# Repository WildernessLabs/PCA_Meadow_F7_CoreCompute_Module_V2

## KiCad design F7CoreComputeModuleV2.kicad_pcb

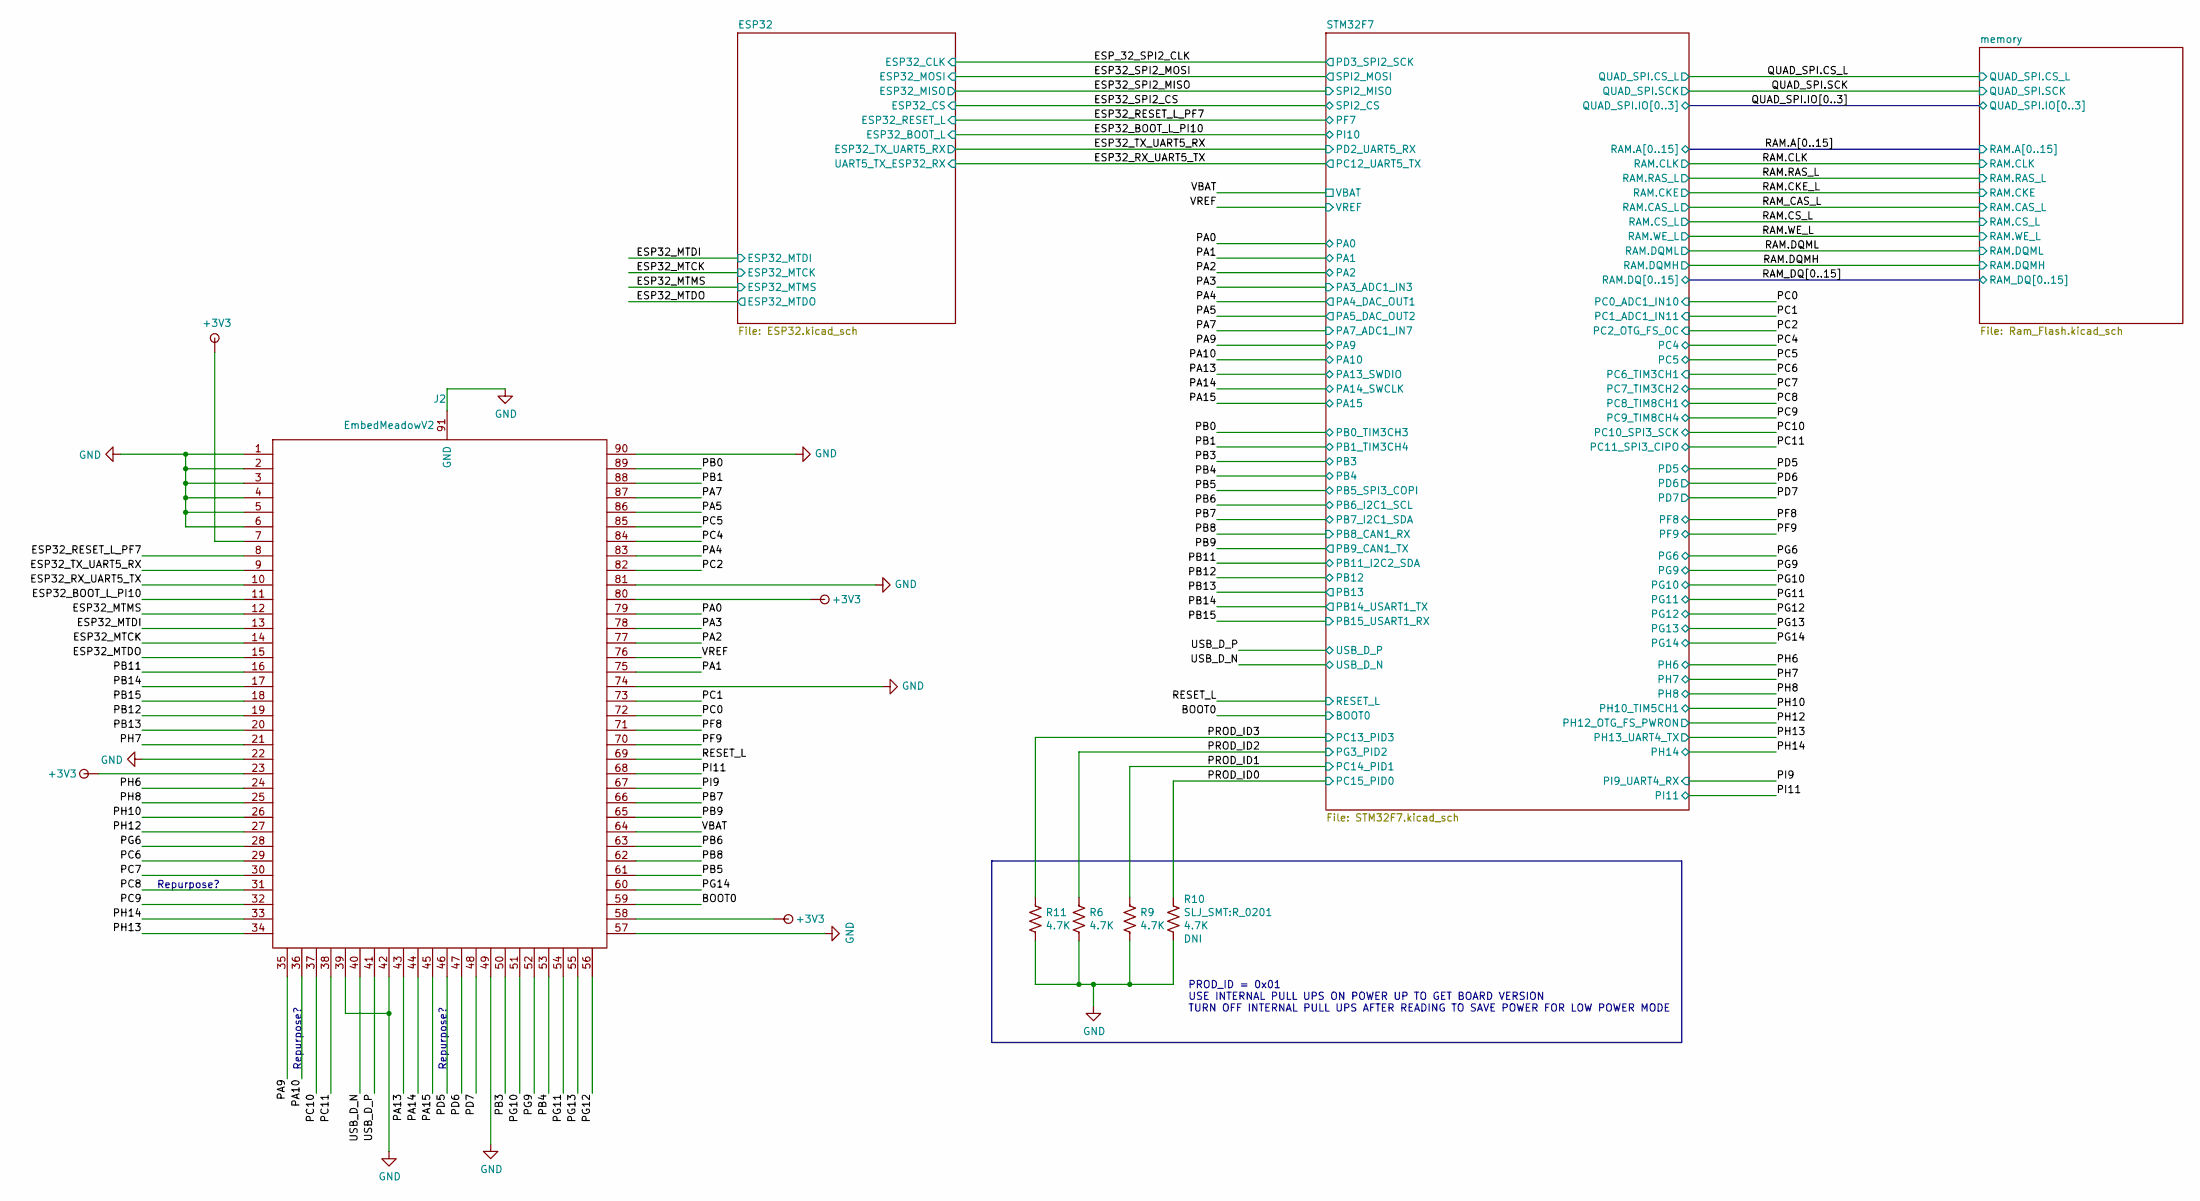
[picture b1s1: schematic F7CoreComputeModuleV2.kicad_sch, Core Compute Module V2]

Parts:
J2: EmbedMeadowV2; MeadowEmbededV2_OnModule
R6, R9, R10, R11: R_4K7_1%_0201; R_0201

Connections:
+3V3: J2.7, J2.23, J2.58, J2.80; also elsewhere on the board
/BOOT0: J2.59; also elsewhere on the board
/ESP32_BOOT_L_PI10: J2.11; also elsewhere on the board
/ESP32_MTCK: J2.14; also elsewhere on the board
/ESP32_MTDI: J2.13; also elsewhere on the board
/ESP32_MTDO: J2.15; also elsewhere on the board
/ESP32_MTMS: J2.12; also elsewhere on the board
/ESP32_RESET_L_PF7: J2.8; also elsewhere on the board
/ESP32_RX_UART5_TX: J2.10; also elsewhere on the board
/ESP32_TX_UART5_RX: J2.9; also elsewhere on the board
/PA0: J2.79; also elsewhere on the board
/PA1: J2.75; also elsewhere on the board
/PA2: J2.77; also elsewhere on the board
/PA3: J2.78; also elsewhere on the board
/PA4: J2.83; also elsewhere on the board
/PA5: J2.86; also elsewhere on the board
/PA7: J2.87; also elsewhere on the board
/PA9: J2.35; also elsewhere on the board
/PA10: J2.36; also elsewhere on the board
/PA13: J2.43; also elsewhere on the board
/PA14: J2.44; also elsewhere on the board
/PA15: J2.45; also elsewhere on the board
/PB0: J2.89; also elsewhere on the board
/PB1: J2.88; also elsewhere on the board
/PB3: J2.50; also elsewhere on the board
/PB4: J2.53; also elsewhere on the board
/PB5: J2.61; also elsewhere on the board
/PB6: J2.63; also elsewhere on the board
/PB7: J2.66; also elsewhere on the board
/PB8: J2.62; also elsewhere on the board
/PB9: J2.65; also elsewhere on the board
/PB11: J2.16; also elsewhere on the board
/PB12: J2.19; also elsewhere on the board
/PB13: J2.20; also elsewhere on the board
/PB14: J2.17; also elsewhere on the board
/PB15: J2.18; also elsewhere on the board
/PC0: J2.72; also elsewhere on the board
/PC1: J2.73; also elsewhere on the board
/PC2: J2.82; also elsewhere on the board
/PC4: J2.84; also elsewhere on the board
/PC5: J2.85; also elsewhere on the board
/PC6: J2.29; also elsewhere on the board
/PC7: J2.30; also elsewhere on the board
/PC8: J2.31; also elsewhere on the board
/PC9: J2.32; also elsewhere on the board
/PC10: J2.37; also elsewhere on the board
/PC11: J2.38; also elsewhere on the board
/PD5: J2.46; also elsewhere on the board
/PD6: J2.47; also elsewhere on the board
/PD7: J2.48; also elsewhere on the board
/PF8: J2.71; also elsewhere on the board
/PF9: J2.70; also elsewhere on the board
/PG6: J2.28; also elsewhere on the board
/PG9: J2.52; also elsewhere on the board
/PG10: J2.51; also elsewhere on the board
/PG11: J2.54; also elsewhere on the board
/PG12: J2.56; also elsewhere on the board
/PG13: J2.55; also elsewhere on the board
/PG14: J2.60; also elsewhere on the board
/PH6: J2.24; also elsewhere on the board
/PH7: J2.21; also elsewhere on the board
/PH8: J2.25; also elsewhere on the board
/PH10: J2.26; also elsewhere on the board
/PH12: J2.27; also elsewhere on the board
/PH13: J2.34; also elsewhere on the board
/PH14: J2.33; also elsewhere on the board
/PI9: J2.67; also elsewhere on the board
/PI11: J2.68; also elsewhere on the board
/PROD_ID0: R10.1; also elsewhere on the board
/PROD_ID1: R9.1; also elsewhere on the board
/PROD_ID2: R6.1; also elsewhere on the board
/PROD_ID3: R11.1; also elsewhere on the board
/RESET_L: J2.69; also elsewhere on the board
/USB_D_N: J2.40; also elsewhere on the board
/USB_D_P: J2.41; also elsewhere on the board
/VBAT: J2.64; also elsewhere on the board
/VREF: J2.76; also elsewhere on the board
GND: J2.1, J2.2, J2.3, J2.4, J2.5, J2.6, J2.22, J2.39, J2.42, J2.49, J2.57, J2.74, J2.81, J2.90, J2.91 (GND), R6.2, R9.2, R10.2, R11.2; also elsewhere on the board

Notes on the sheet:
PROD_ID = 0x01 USE INTERNAL PULL UPS ON POWER UP TO GET BOARD VERSION TURN OFF INTERNAL PULL UPS AFTER READING TO SAVE POWER FOR LOW POWER MODE
Repurpose?

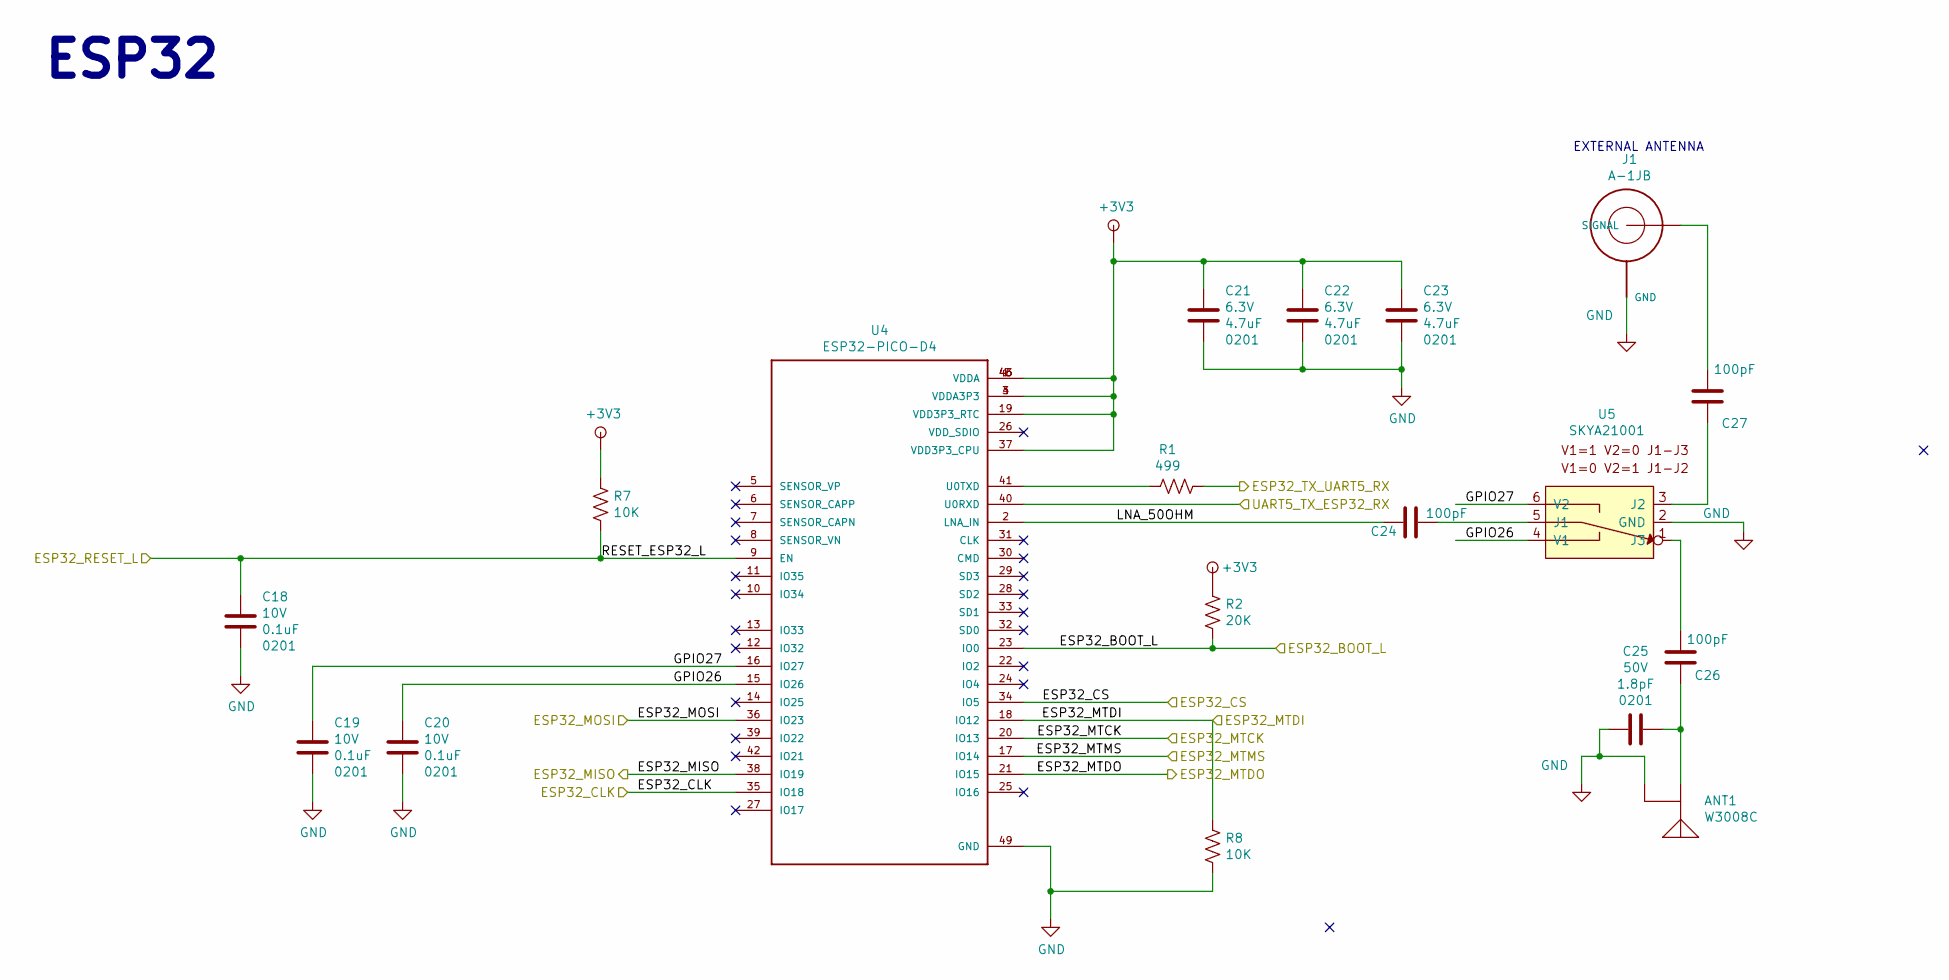
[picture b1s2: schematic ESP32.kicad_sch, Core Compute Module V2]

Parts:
ANT1: W3008C; ANTENNA_W3008C_B
C18, C19, C20: C_0201_0.1UF_10V_X5R; C_0201; Voltage 10V; Tolerance 10%
C21, C22, C23: C_0201_4.7UF_6.3V_X5R; C_0201; Voltage 6.3V; Tolerance 20%
C24, C26, C27: C_0201_100PF_50V_C0G; C_0201; Voltage 50V; Tolerance 5%
C25: C_0201_1.8pF_50V_C0G; C_0201; Voltage 50V; Tolerance 0.25pF
J1: A-1JB; AMPHENOL_A-1JB
R1: R_499_1%_0201; R_0201
R2: R_20K_1%_0201; R_0201
R7, R8: R_10K_1%_0201; R_0201
U4: ESP32-PICO-D4; PQFN50P700X700X104-49N
U5: SKYA21001; SOT-363_SC-70-6

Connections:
+3V3: C21.1, C22.1, C23.1, R2.1, R7.1, U4.1 (VDDA), U4.3 (VDDA3P3), U4.4 (VDDA3P3), U4.19 (VDD3P3_RTC), U4.37 (VDD3P3_CPU), U4.43 (VDDA), U4.46 (VDDA); also elsewhere on the board
/ESP32/GPIO26: C20.1, U4.15 (IO26), U5.4 (V1)
/ESP32/GPIO27: C19.1, U4.16 (IO27), U5.6 (V2)
/ESP32/LNA_50OHM: C24.2, U4.2 (LNA_IN)
/ESP32_BOOT_L_PI10: R2.2, U4.23 (IO0); also elsewhere on the board
/ESP32_MTCK: U4.20 (IO13); also elsewhere on the board
/ESP32_MTDI: R8.1, U4.18 (IO12); also elsewhere on the board
/ESP32_MTDO: U4.21 (IO15); also elsewhere on the board
/ESP32_MTMS: U4.17 (IO14); also elsewhere on the board
/ESP32_RESET_L_PF7: C18.1, R7.2, U4.9 (EN); also elsewhere on the board
/ESP32_RX_UART5_TX: U4.40 (U0RXD); also elsewhere on the board
/ESP32_SPI2_CS: U4.34 (IO5); also elsewhere on the board
/ESP32_SPI2_MISO: U4.38 (IO19); also elsewhere on the board
/ESP32_SPI2_MOSI: U4.36 (IO23); also elsewhere on the board
/ESP32_TX_UART5_RX: R1.1; also elsewhere on the board
/ESP_32_SPI2_CLK: U4.35 (IO18); also elsewhere on the board
GND: ANT1.G1 (GND), ANT1.G2 (GND), C18.2, C19.2, C20.2, C21.2, C22.2, C23.2, C25.2, J1.GND1 (GND), J1.GND2 (GND), J1.OPTIONAL_GND (GND), R8.2, U4.49 (GND), U5.2 (GND); also elsewhere on the board
unnamed: ANT1.FEED, C25.1, C26.1
unnamed: C24.1, U5.5 (J1)
unnamed: C26.2, U5.1 (J3)
unnamed: C27.1, U5.3 (J2)
unnamed: C27.2, J1.SIGNAL
unnamed: R1.2, U4.41 (U0TXD)

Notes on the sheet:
ESP32
EXTERNAL ANTENNA

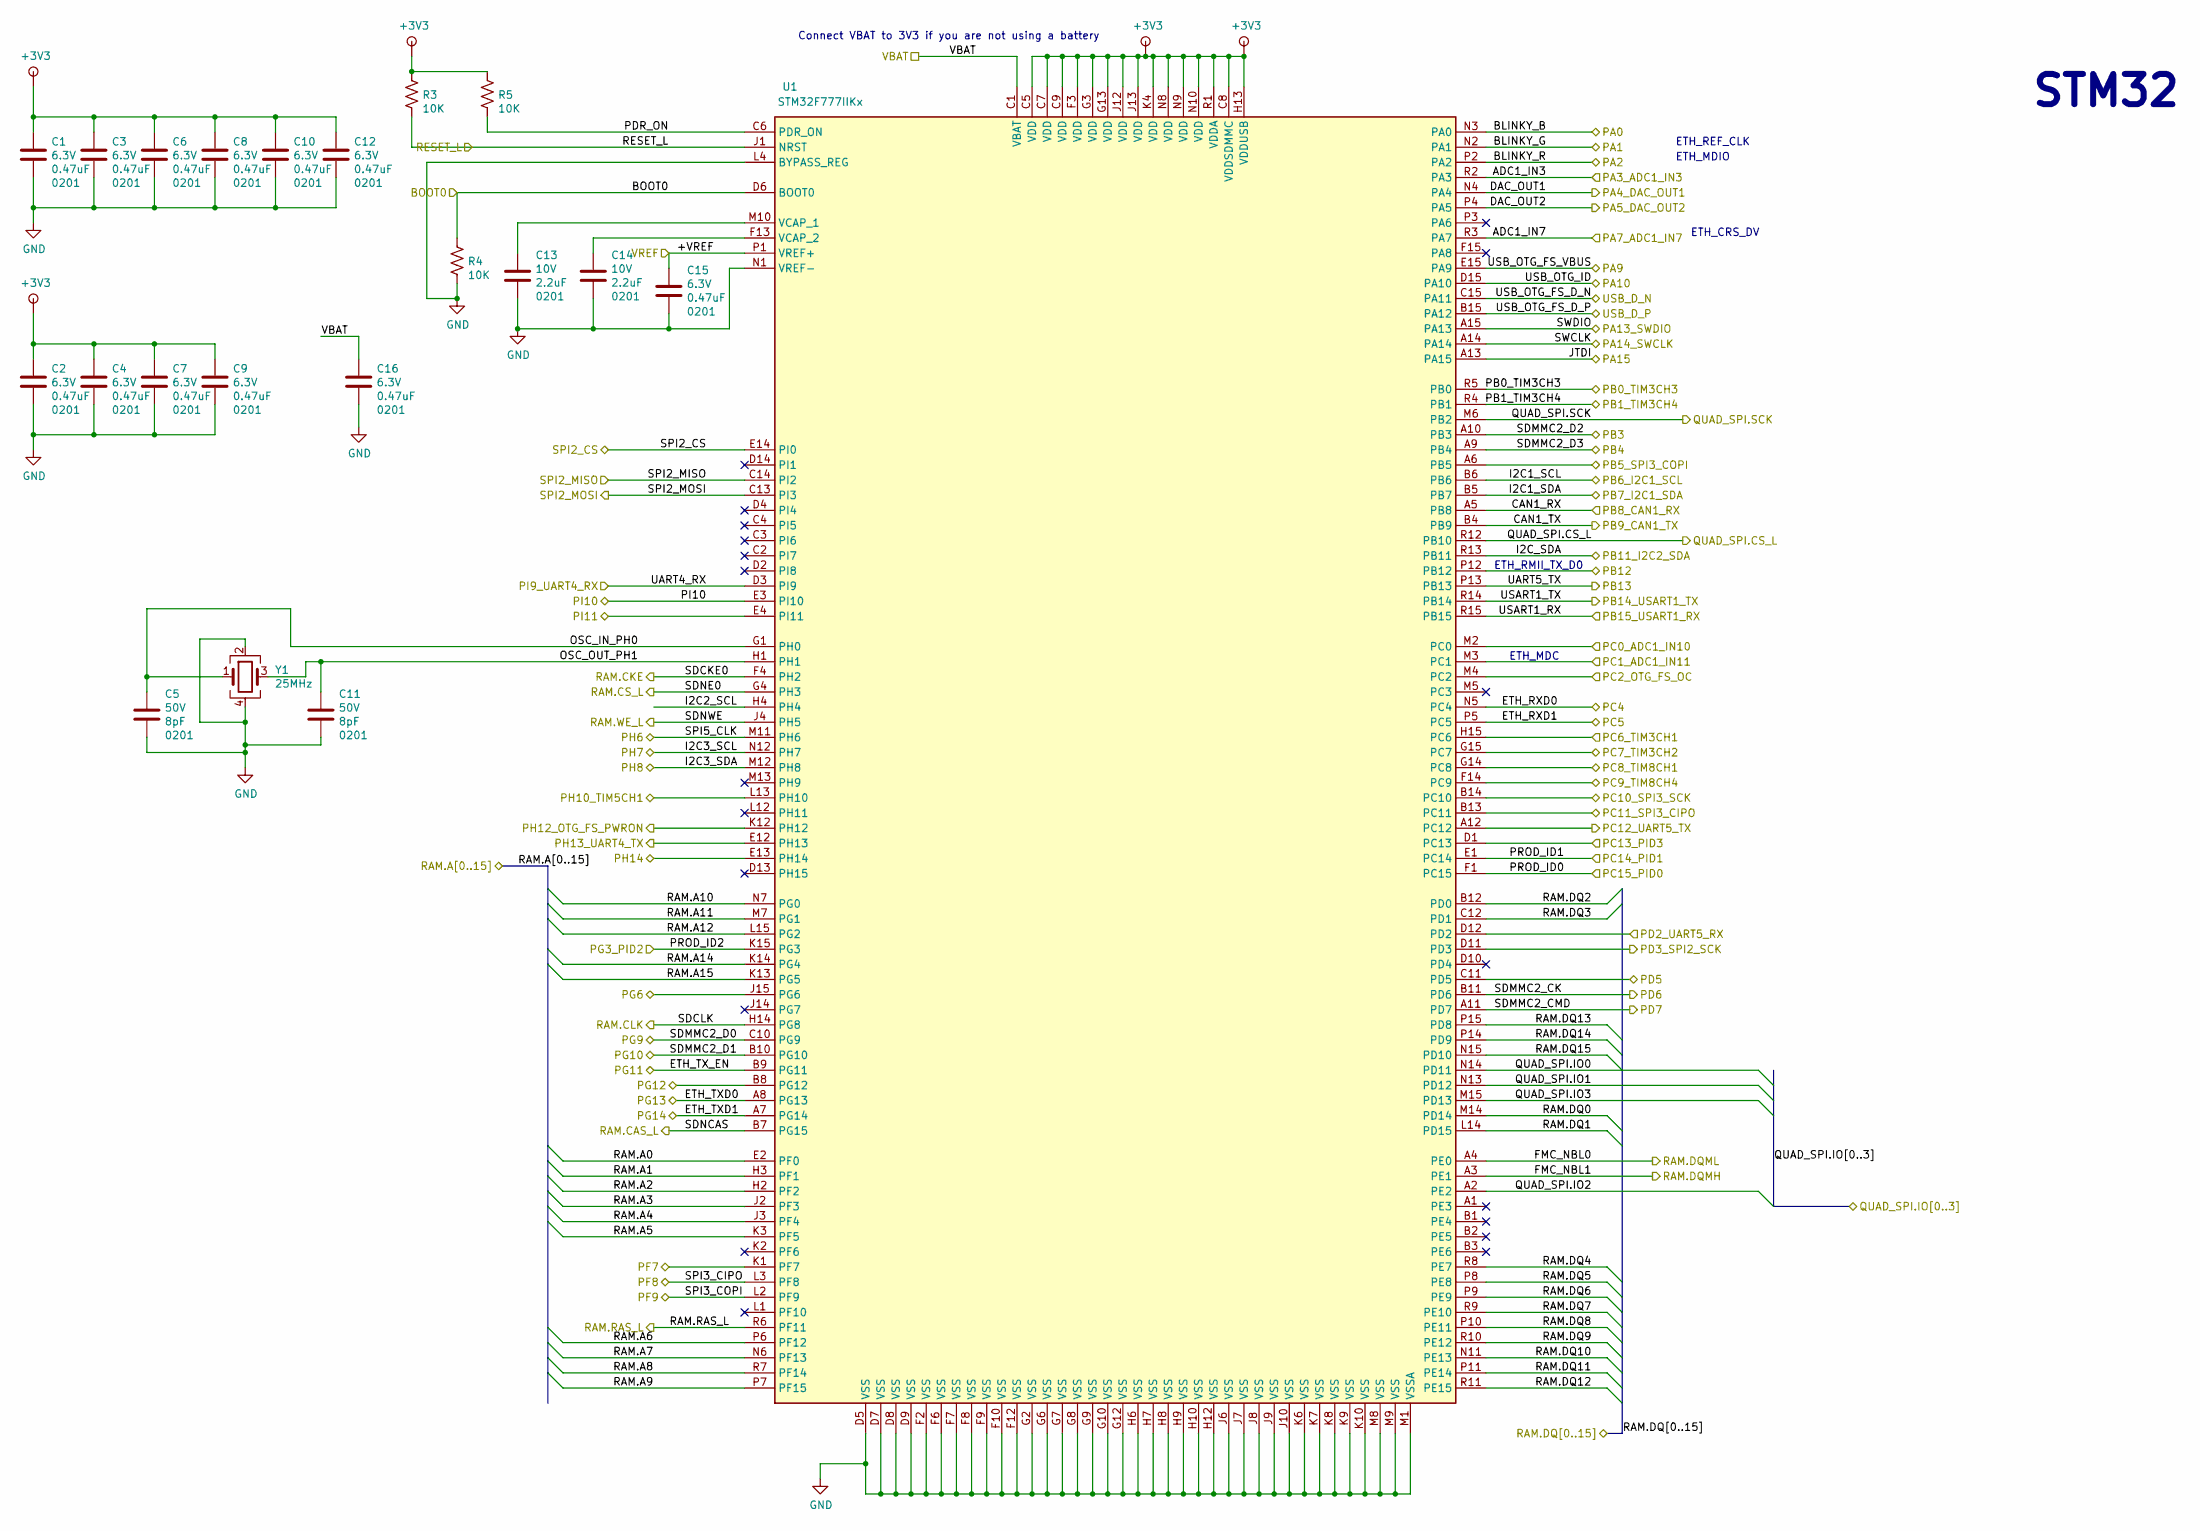
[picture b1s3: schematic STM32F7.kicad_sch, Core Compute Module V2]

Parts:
C1, C2, C3, C4, C6, C7, C8, C9, C10, C12, C15, C16: C_0201_0.47UF_6.3V_X5R; C_0201; Voltage 6.3V; Tolerance 10%
C5, C11: C_0201_8pF_50V_C0G; C_0201; Voltage 50V; Tolerance 0.5pF
C13, C14: C_0201_2.2UF_10V_X5R; C_0201; Voltage 10V; Tolerance 10%
R3, R4, R5: R_10K_1%_0201; R_0201
U1: STM32F777IIKx; UFBGA-201_10x10mm_Layout15x15_P0.65mm
Y1: ABM12W-25.0000MHZ-6-B1U-T3; XTAL_ABM12W-24.0000MHZ-6-B1U-T3

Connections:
+3V3: C1.1, C2.1, C3.1, C4.1, C6.1, C7.1, C8.1, C9.1, C10.1, C12.1, R3.1, R5.1, U1.C5 (VDD), U1.C7 (VDD), U1.C8 (VDDSDMMC), U1.C9 (VDD), U1.F3 (VDD), U1.G3 (VDD), U1.G13 (VDD), U1.H13 (VDDUSB), U1.J12 (VDD), U1.J13 (VDD), U1.K4 (VDD), U1.N8 (VDD), U1.N9 (VDD), U1.N10 (VDD), U1.R1 (VDDA); also elsewhere on the board
/BOOT0: R4.1, U1.D6 (BOOT0); also elsewhere on the board
/ESP32_BOOT_L_PI10: U1.E3 (PI10); also elsewhere on the board
/ESP32_RESET_L_PF7: U1.K1 (PF7); also elsewhere on the board
/ESP32_RX_UART5_TX: U1.A12 (PC12); also elsewhere on the board
/ESP32_SPI2_CS: U1.E14 (PI0); also elsewhere on the board
/ESP32_SPI2_MISO: U1.C14 (PI2); also elsewhere on the board
/ESP32_SPI2_MOSI: U1.C13 (PI3); also elsewhere on the board
/ESP32_TX_UART5_RX: U1.D12 (PD2); also elsewhere on the board
/ESP_32_SPI2_CLK: U1.D11 (PD3); also elsewhere on the board
/PA0: U1.N3 (PA0); also elsewhere on the board
/PA1: U1.N2 (PA1); also elsewhere on the board
/PA2: U1.P2 (PA2); also elsewhere on the board
/PA3: U1.R2 (PA3); also elsewhere on the board
/PA4: U1.N4 (PA4); also elsewhere on the board
/PA5: U1.P4 (PA5); also elsewhere on the board
/PA7: U1.R3 (PA7); also elsewhere on the board
/PA9: U1.E15 (PA9); also elsewhere on the board
/PA10: U1.D15 (PA10); also elsewhere on the board
/PA13: U1.A15 (PA13); also elsewhere on the board
/PA14: U1.A14; also elsewhere on the board
/PA15: U1.A13 (PA15); also elsewhere on the board
/PB0: U1.R5 (PB0); also elsewhere on the board
/PB1: U1.R4 (PB1); also elsewhere on the board
/PB3: U1.A10 (PB3); also elsewhere on the board
/PB4: U1.A9 (PB4); also elsewhere on the board
/PB5: U1.A6 (PB5); also elsewhere on the board
/PB6: U1.B6; also elsewhere on the board
/PB7: U1.B5 (PB7); also elsewhere on the board
/PB8: U1.A5 (PB8); also elsewhere on the board
/PB9: U1.B4 (PB9); also elsewhere on the board
/PB11: U1.R13 (PB11); also elsewhere on the board
/PB12: U1.P12 (PB12); also elsewhere on the board
/PB13: U1.P13 (PB13); also elsewhere on the board
/PB14: U1.R14 (PB14); also elsewhere on the board
/PB15: U1.R15 (PB15); also elsewhere on the board
/PC0: U1.M2 (PC0); also elsewhere on the board
/PC1: U1.M3 (PC1); also elsewhere on the board
/PC2: U1.M4 (PC2); also elsewhere on the board
/PC4: U1.N5 (PC4); also elsewhere on the board
/PC5: U1.P5 (PC5); also elsewhere on the board
/PC6: U1.H15 (PC6); also elsewhere on the board
/PC7: U1.G15 (PC7); also elsewhere on the board
/PC8: U1.G14 (PC8); also elsewhere on the board
/PC9: U1.F14 (PC9); also elsewhere on the board
/PC10: U1.B14 (PC10); also elsewhere on the board
/PC11: U1.B13 (PC11); also elsewhere on the board
/PD5: U1.C11 (PD5); also elsewhere on the board
/PD6: U1.B11 (PD6); also elsewhere on the board
/PD7: U1.A11 (PD7); also elsewhere on the board
/PF8: U1.L3 (PF8); also elsewhere on the board
/PF9: U1.L2 (PF9); also elsewhere on the board
/PG6: U1.J15 (PG6); also elsewhere on the board
/PG9: U1.C10 (PG9); also elsewhere on the board
/PG10: U1.B10 (PG10); also elsewhere on the board
/PG11: U1.B9 (PG11); also elsewhere on the board
/PG12: U1.B8 (PG12); also elsewhere on the board
/PG13: U1.A8 (PG13); also elsewhere on the board
/PG14: U1.A7 (PG14); also elsewhere on the board
/PH6: U1.M11 (PH6); also elsewhere on the board
/PH7: U1.N12 (PH7); also elsewhere on the board
/PH8: U1.M12 (PH8); also elsewhere on the board
/PH10: U1.L13 (PH10); also elsewhere on the board
/PH12: U1.K12 (PH12); also elsewhere on the board
/PH13: U1.E12 (PH13); also elsewhere on the board
/PH14: U1.E13 (PH14); also elsewhere on the board
/PI9: U1.D3 (PI9); also elsewhere on the board
/PI11: U1.E4 (PI11); also elsewhere on the board
/PROD_ID0: U1.F1 (PC15); also elsewhere on the board
/PROD_ID1: U1.E1 (PC14); also elsewhere on the board
/PROD_ID2: U1.K15 (PG3); also elsewhere on the board
/PROD_ID3: U1.D1 (PC13); also elsewhere on the board
/QUAD_SPI.CS_L: U1.R12 (PB10); also elsewhere on the board
/QUAD_SPI.SCK: U1.M6 (PB2); also elsewhere on the board
/RAM.CKE_L: U1.F4 (PH2); also elsewhere on the board
/RAM.CLK: U1.H14 (PG8); also elsewhere on the board
/RAM.CS_L: U1.G4 (PH3); also elsewhere on the board
/RAM.DQMH: U1.A3 (PE1); also elsewhere on the board
/RAM.DQML: U1.A4 (PE0); also elsewhere on the board
/RAM.RAS_L: U1.R6 (PF11); also elsewhere on the board
/RAM.WE_L: U1.J4 (PH5); also elsewhere on the board
/RAM_CAS_L: U1.B7 (PG15); also elsewhere on the board
/RESET_L: R3.2, U1.J1 (NRST); also elsewhere on the board
/STM32F7/I2C2_SCL: U1.H4
/STM32F7/OSC_IN_PH0: C5.1, U1.G1 (PH0), Y1.1
/STM32F7/OSC_OUT_PH1: C11.1, U1.H1, Y1.3
/STM32F7/PDR_ON: R5.2, U1.C6 (PDR_ON)
/STM32F7/QUAD_SPI.IO0: U1.N14 (PD11); also elsewhere on the board
/STM32F7/QUAD_SPI.IO1: U1.N13 (PD12); also elsewhere on the board
/STM32F7/QUAD_SPI.IO2: U1.A2 (PE2); also elsewhere on the board
/STM32F7/QUAD_SPI.IO3: U1.M15 (PD13); also elsewhere on the board
/STM32F7/RAM.A0: U1.E2 (PF0); also elsewhere on the board
/STM32F7/RAM.A1: U1.H3 (PF1); also elsewhere on the board
/STM32F7/RAM.A2: U1.H2 (PF2); also elsewhere on the board
/STM32F7/RAM.A3: U1.J2 (PF3); also elsewhere on the board
/STM32F7/RAM.A4: U1.J3 (PF4); also elsewhere on the board
/STM32F7/RAM.A5: U1.K3 (PF5); also elsewhere on the board
/STM32F7/RAM.A6: U1.P6 (PF12); also elsewhere on the board
/STM32F7/RAM.A7: U1.N6 (PF13); also elsewhere on the board
/STM32F7/RAM.A8: U1.R7 (PF14); also elsewhere on the board
/STM32F7/RAM.A9: U1.P7 (PF15); also elsewhere on the board
/STM32F7/RAM.A10: U1.N7 (PG0); also elsewhere on the board
/STM32F7/RAM.A11: U1.M7 (PG1); also elsewhere on the board
/STM32F7/RAM.A12: U1.L15 (PG2); also elsewhere on the board
/STM32F7/RAM.A14: U1.K14 (PG4); also elsewhere on the board
/STM32F7/RAM.A15: U1.K13 (PG5); also elsewhere on the board
/STM32F7/RAM.DQ0: U1.M14 (PD14); also elsewhere on the board
/STM32F7/RAM.DQ1: U1.L14 (PD15); also elsewhere on the board
/STM32F7/RAM.DQ2: U1.B12 (PD0); also elsewhere on the board
/STM32F7/RAM.DQ3: U1.C12 (PD1); also elsewhere on the board
/STM32F7/RAM.DQ4: U1.R8 (PE7); also elsewhere on the board
/STM32F7/RAM.DQ5: U1.P8 (PE8); also elsewhere on the board
/STM32F7/RAM.DQ6: U1.P9 (PE9); also elsewhere on the board
/STM32F7/RAM.DQ7: U1.R9 (PE10); also elsewhere on the board
/STM32F7/RAM.DQ8: U1.P10 (PE11); also elsewhere on the board
/STM32F7/RAM.DQ9: U1.R10 (PE12); also elsewhere on the board
/STM32F7/RAM.DQ10: U1.N11 (PE13); also elsewhere on the board
/STM32F7/RAM.DQ11: U1.P11 (PE14); also elsewhere on the board
/STM32F7/RAM.DQ12: U1.R11 (PE15); also elsewhere on the board
/STM32F7/RAM.DQ13: U1.P15 (PD8); also elsewhere on the board
/STM32F7/RAM.DQ14: U1.P14 (PD9); also elsewhere on the board
/STM32F7/RAM.DQ15: U1.N15 (PD10); also elsewhere on the board
/USB_D_N: U1.C15 (PA11); also elsewhere on the board
/USB_D_P: U1.B15 (PA12); also elsewhere on the board
/VBAT: C16.1, U1.C1 (VBAT); also elsewhere on the board
/VREF: C15.1, U1.P1 (VREF+); also elsewhere on the board
GND: C1.2, C2.2, C3.2, C4.2, C5.2, C6.2, C7.2, C8.2, C9.2, C10.2, C11.2, C12.2, C13.2, C14.2, C15.2, C16.2, R4.2, U1.D5 (VSS), U1.D7 (VSS), U1.D8 (VSS), U1.D9 (VSS), U1.F2 (VSS), U1.F6 (VSS), U1.F7 (VSS), U1.F8 (VSS), U1.F9 (VSS), U1.F10 (VSS), U1.F12 (VSS), U1.G2 (VSS), U1.G6 (VSS), U1.G7 (VSS), U1.G8 (VSS), U1.G9 (VSS), U1.G10 (VSS), U1.G12 (VSS), U1.H6 (VSS), U1.H7 (VSS), U1.H8 (VSS), U1.H9 (VSS), U1.H10 (VSS), U1.H12 (VSS), U1.J6 (VSS), U1.J7 (VSS), U1.J8 (VSS), U1.J9 (VSS), U1.J10 (VSS), U1.K6 (VSS), U1.K7 (VSS), U1.K8 (VSS), U1.K9 (VSS), U1.K10 (VSS), U1.L4 (BYPASS_REG), U1.M1 (VSSA), U1.M8 (VSS), U1.M9 (VSS), U1.N1 (VREF-), Y1.2, Y1.4; also elsewhere on the board
unnamed: C13.1, U1.M10 (VCAP_1)
unnamed: C14.1, U1.F13 (VCAP_2)

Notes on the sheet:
ETH_RMII_TX_D0
Connect VBAT to 3V3 if you are not using a battery
ETH_REF_CLK
ETH_CRS_DV
ETH_MDIO
STM32
ETH_MDC

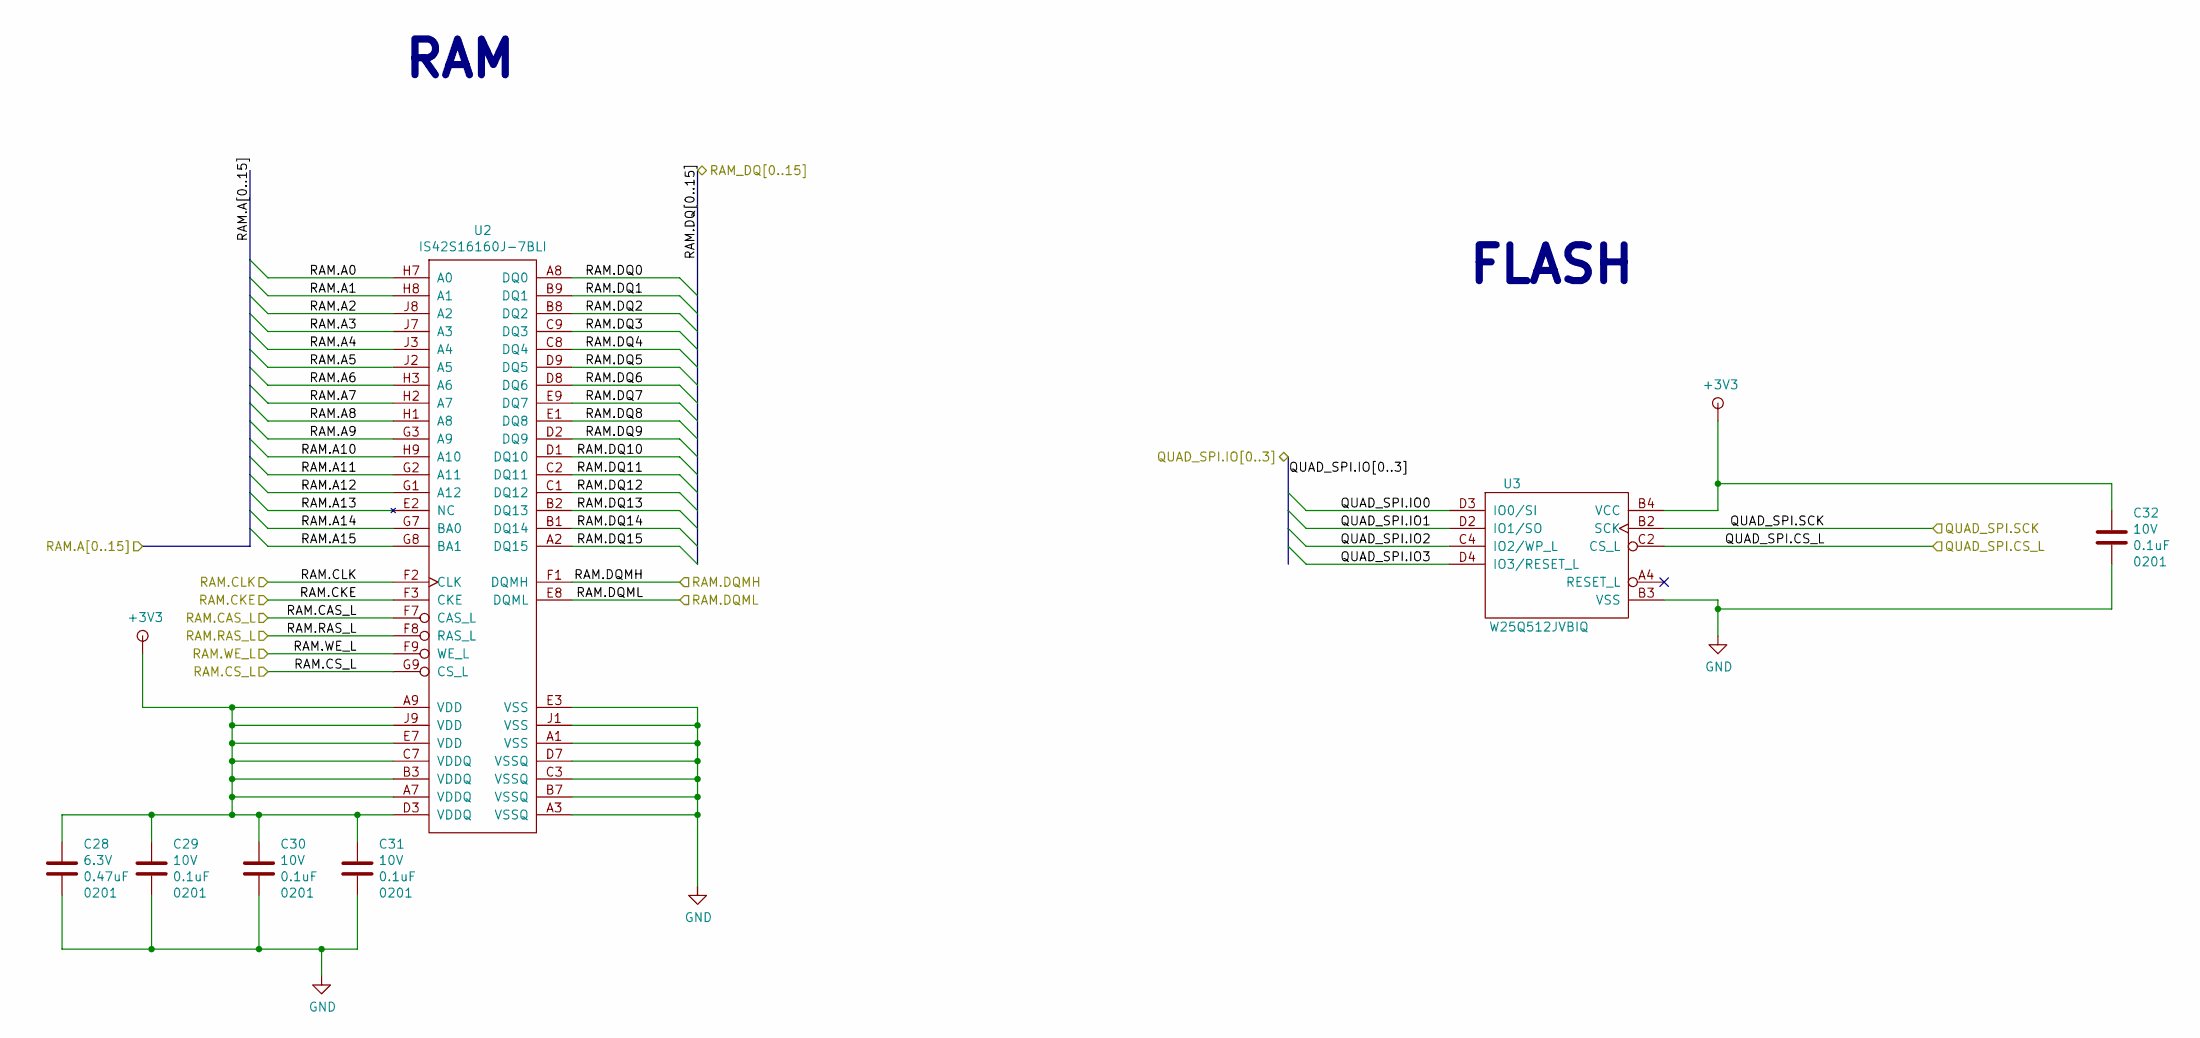
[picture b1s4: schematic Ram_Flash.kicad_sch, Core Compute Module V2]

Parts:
C28: C_0201_0.47UF_6.3V_X5R; C_0201; Voltage 6.3V; Tolerance 10%
C29, C30, C31, C32: C_0201_0.1UF_10V_X5R; C_0201; Voltage 10V; Tolerance 10%
U2: IS42S16160J-7BLI; TFBGA-54
U3: W25Q512JVBIQ; BGA24C100P6X4_800X600X120N

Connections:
+3V3: C28.1, C29.1, C30.1, C31.1, C32.1, U2.A7 (VDDQ), U2.A9 (VDD), U2.B3 (VDDQ), U2.C7 (VDDQ), U2.D3 (VDDQ), U2.E7 (VDD), U2.J9 (VDD), U3.B4 (VCC); also elsewhere on the board
/QUAD_SPI.CS_L: U3.C2 (CS_L); also elsewhere on the board
/QUAD_SPI.SCK: U3.B2 (SCK); also elsewhere on the board
/RAM.CKE_L: U2.F3 (CKE); also elsewhere on the board
/RAM.CLK: U2.F2 (CLK); also elsewhere on the board
/RAM.CS_L: U2.G9 (CS_L); also elsewhere on the board
/RAM.DQMH: U2.F1 (DQMH); also elsewhere on the board
/RAM.DQML: U2.E8 (DQML); also elsewhere on the board
/RAM.RAS_L: U2.F8 (RAS_L); also elsewhere on the board
/RAM.WE_L: U2.F9 (WE_L); also elsewhere on the board
/RAM_CAS_L: U2.F7 (CAS_L); also elsewhere on the board
/STM32F7/QUAD_SPI.IO0: U3.D3 (IO0/SI); also elsewhere on the board
/STM32F7/QUAD_SPI.IO1: U3.D2 (IO1/SO); also elsewhere on the board
/STM32F7/QUAD_SPI.IO2: U3.C4 (IO2/WP_L); also elsewhere on the board
/STM32F7/QUAD_SPI.IO3: U3.D4 (IO3/RESET_L); also elsewhere on the board
/STM32F7/RAM.A0: U2.H7 (A0); also elsewhere on the board
/STM32F7/RAM.A1: U2.H8 (A1); also elsewhere on the board
/STM32F7/RAM.A2: U2.J8 (A2); also elsewhere on the board
/STM32F7/RAM.A3: U2.J7 (A3); also elsewhere on the board
/STM32F7/RAM.A4: U2.J3 (A4); also elsewhere on the board
/STM32F7/RAM.A5: U2.J2 (A5); also elsewhere on the board
/STM32F7/RAM.A6: U2.H3 (A6); also elsewhere on the board
/STM32F7/RAM.A7: U2.H2 (A7); also elsewhere on the board
/STM32F7/RAM.A8: U2.H1 (A8); also elsewhere on the board
/STM32F7/RAM.A9: U2.G3 (A9); also elsewhere on the board
/STM32F7/RAM.A10: U2.H9 (A10); also elsewhere on the board
/STM32F7/RAM.A11: U2.G2 (A11); also elsewhere on the board
/STM32F7/RAM.A12: U2.G1 (A12); also elsewhere on the board
/STM32F7/RAM.A14: U2.G7 (BA0); also elsewhere on the board
/STM32F7/RAM.A15: U2.G8 (BA1); also elsewhere on the board
/STM32F7/RAM.DQ0: U2.A8 (DQ0); also elsewhere on the board
/STM32F7/RAM.DQ1: U2.B9 (DQ1); also elsewhere on the board
/STM32F7/RAM.DQ2: U2.B8 (DQ2); also elsewhere on the board
/STM32F7/RAM.DQ3: U2.C9 (DQ3); also elsewhere on the board
/STM32F7/RAM.DQ4: U2.C8 (DQ4); also elsewhere on the board
/STM32F7/RAM.DQ5: U2.D9 (DQ5); also elsewhere on the board
/STM32F7/RAM.DQ6: U2.D8 (DQ6); also elsewhere on the board
/STM32F7/RAM.DQ7: U2.E9 (DQ7); also elsewhere on the board
/STM32F7/RAM.DQ8: U2.E1 (DQ8); also elsewhere on the board
/STM32F7/RAM.DQ9: U2.D2 (DQ9); also elsewhere on the board
/STM32F7/RAM.DQ10: U2.D1 (DQ10); also elsewhere on the board
/STM32F7/RAM.DQ11: U2.C2 (DQ11); also elsewhere on the board
/STM32F7/RAM.DQ12: U2.C1 (DQ12); also elsewhere on the board
/STM32F7/RAM.DQ13: U2.B2 (DQ13); also elsewhere on the board
/STM32F7/RAM.DQ14: U2.B1 (DQ14); also elsewhere on the board
/STM32F7/RAM.DQ15: U2.A2 (DQ15); also elsewhere on the board
/memory/RAM.A13: U2.E2 (NC)
GND: C28.2, C29.2, C30.2, C31.2, C32.2, U2.A1 (VSS), U2.A3 (VSSQ), U2.B7 (VSSQ), U2.C3 (VSSQ), U2.D7 (VSSQ), U2.E3 (VSS), U2.J1 (VSS), U3.B3 (VSS); also elsewhere on the board

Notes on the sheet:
FLASH
RAM

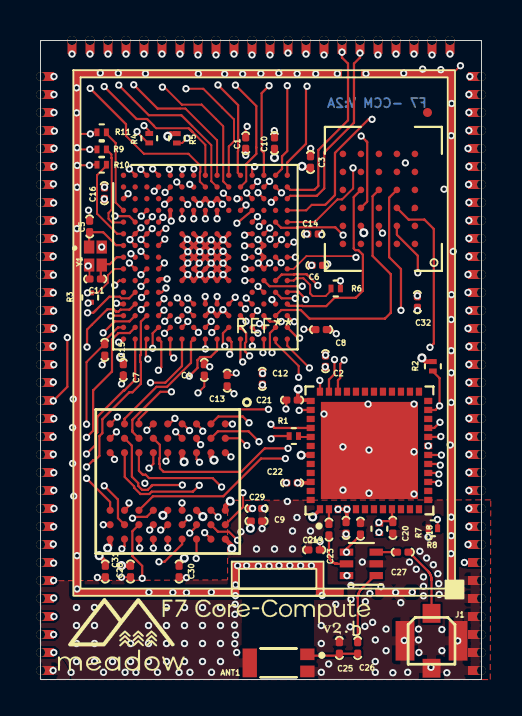
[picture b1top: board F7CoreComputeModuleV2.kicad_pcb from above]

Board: 8 copper layers, 24.5 x 35.5 mm, 51 parts (0 on the bottom side), 141 nets.

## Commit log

2021-01-16 created
2021-07-13 Started Schematic design
2021-07-26 finsihed for the day, cleaned up layout and got pins added
2021-07-26 clean up
2021-07-28 Getting footprint finalized
2021-08-03 LAst commit beforw swapping to smaller unit
2021-08-03 cleaning things up
2021-08-03 Move workign director to git, this is mostly routed core compute module
2021-08-03 added folder structure
2021-08-08 Finished routing, just some clean up and making gerbers
2021-08-09 Should have all files to make V2A
2021-08-09 Small unsaved schematic edit
2021-08-15 Cleaned up footprint drawing
2021-08-15 Added a new layer ECO1, use this layer if you only want the Logo on the top silk layer
2022-02-02 Fixed schematic and added CAD files
2023-01-06 Added pinout spreadsheet
2023-01-08 Added Pin diagram and extra pin infomation.
2023-01-11 More pin defintions added.
2023-01-11 More pin updates
2023-03-07 Added panel gerbers
2023-05-12 syncing my local with main
2023-05-12 gitignore to ignore backups
2023-05-12 remove backup folder
2023-07-29 added shield can start of new REV
2023-08-06 added layer DRC rules, and some constarint changes
2023-08-07 convert to latest kicad version 7.0.7, routed the ram back
2023-08-12 most routing complete
2023-08-13 cleared up all DRC violations
2023-08-14 V2B Gerbers added
